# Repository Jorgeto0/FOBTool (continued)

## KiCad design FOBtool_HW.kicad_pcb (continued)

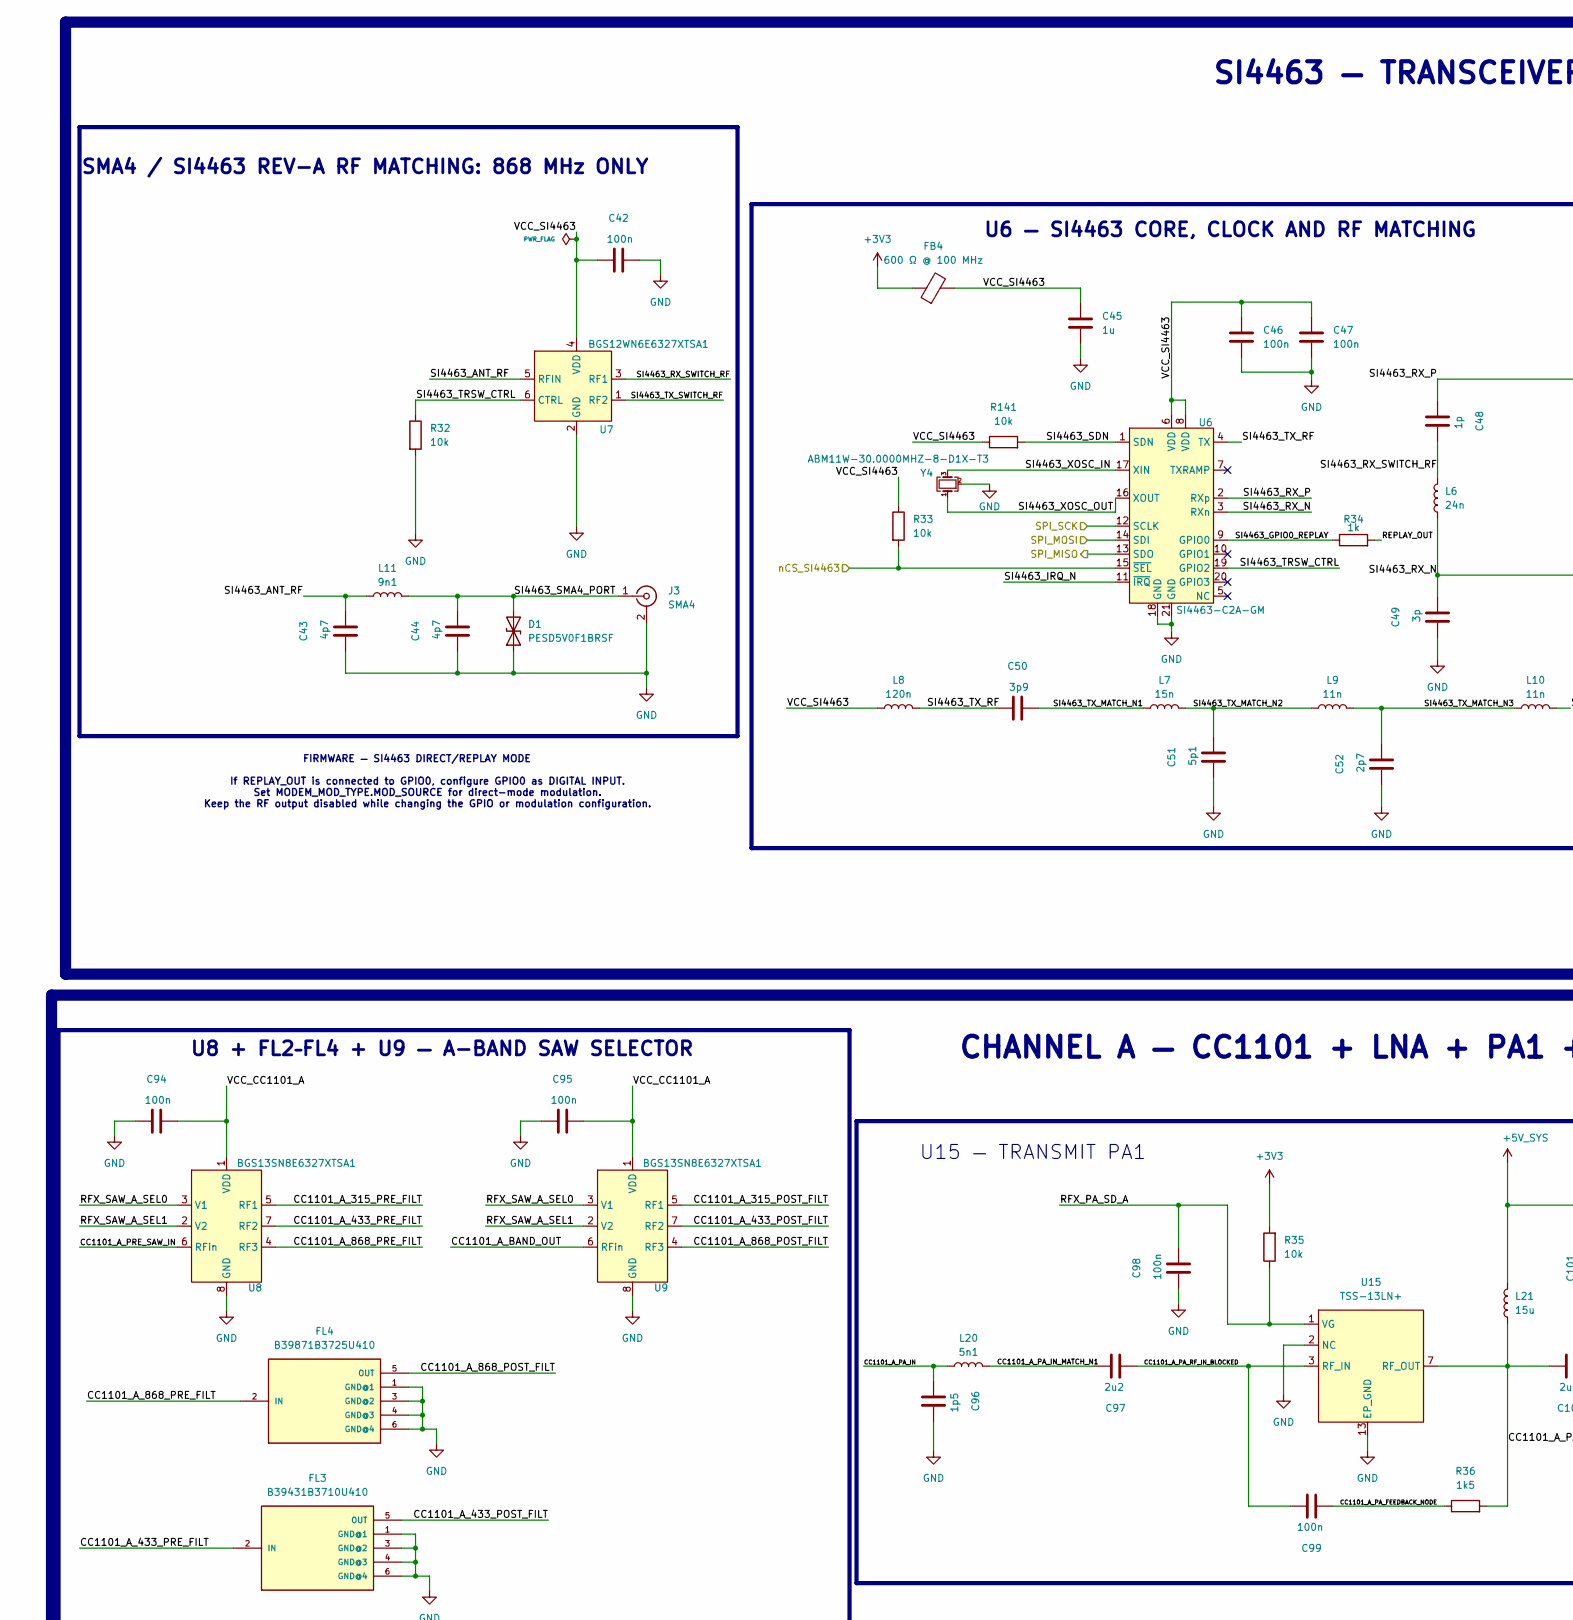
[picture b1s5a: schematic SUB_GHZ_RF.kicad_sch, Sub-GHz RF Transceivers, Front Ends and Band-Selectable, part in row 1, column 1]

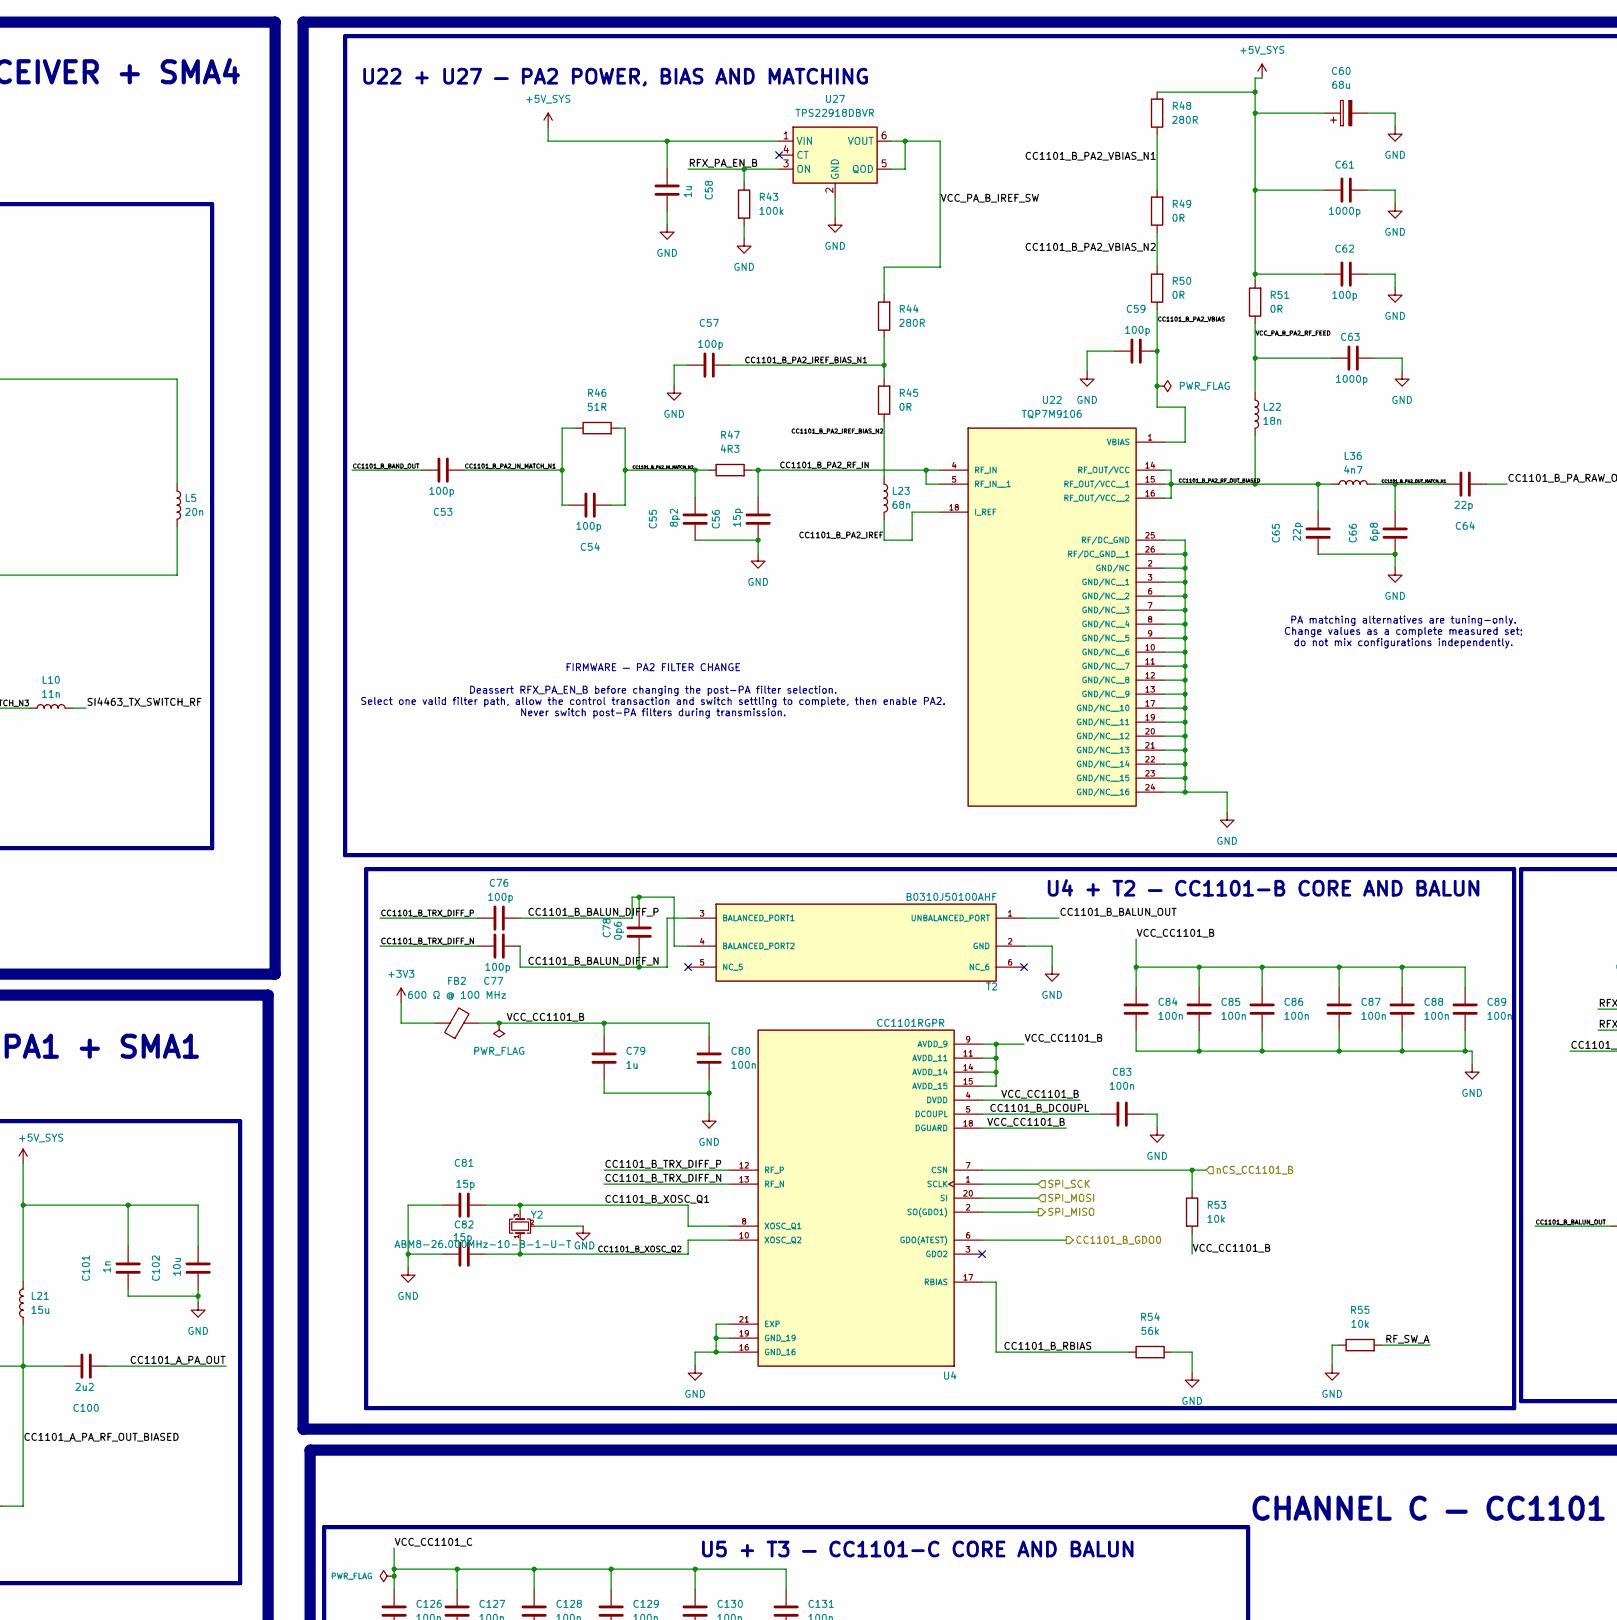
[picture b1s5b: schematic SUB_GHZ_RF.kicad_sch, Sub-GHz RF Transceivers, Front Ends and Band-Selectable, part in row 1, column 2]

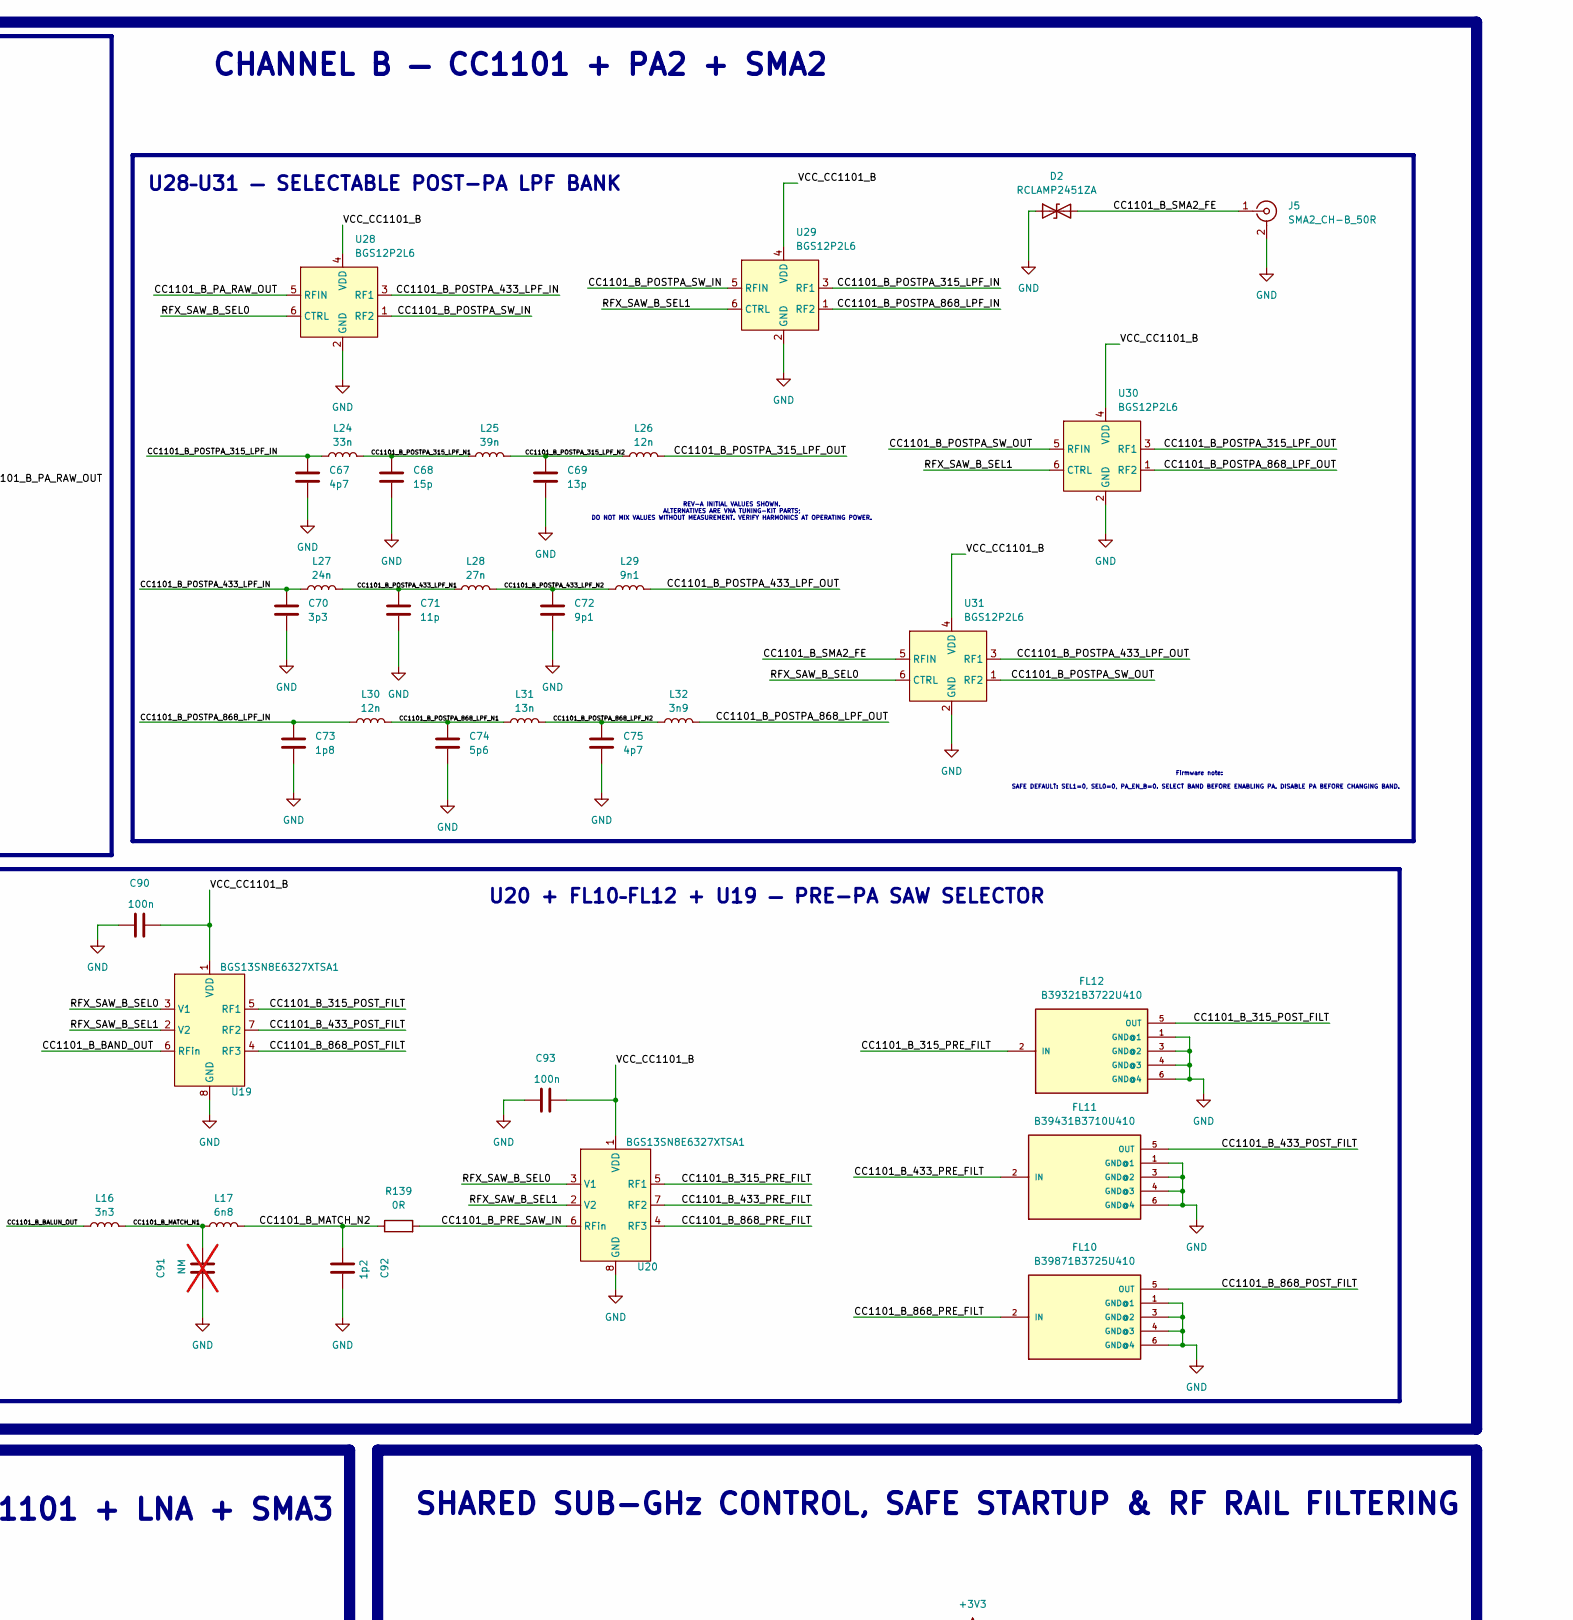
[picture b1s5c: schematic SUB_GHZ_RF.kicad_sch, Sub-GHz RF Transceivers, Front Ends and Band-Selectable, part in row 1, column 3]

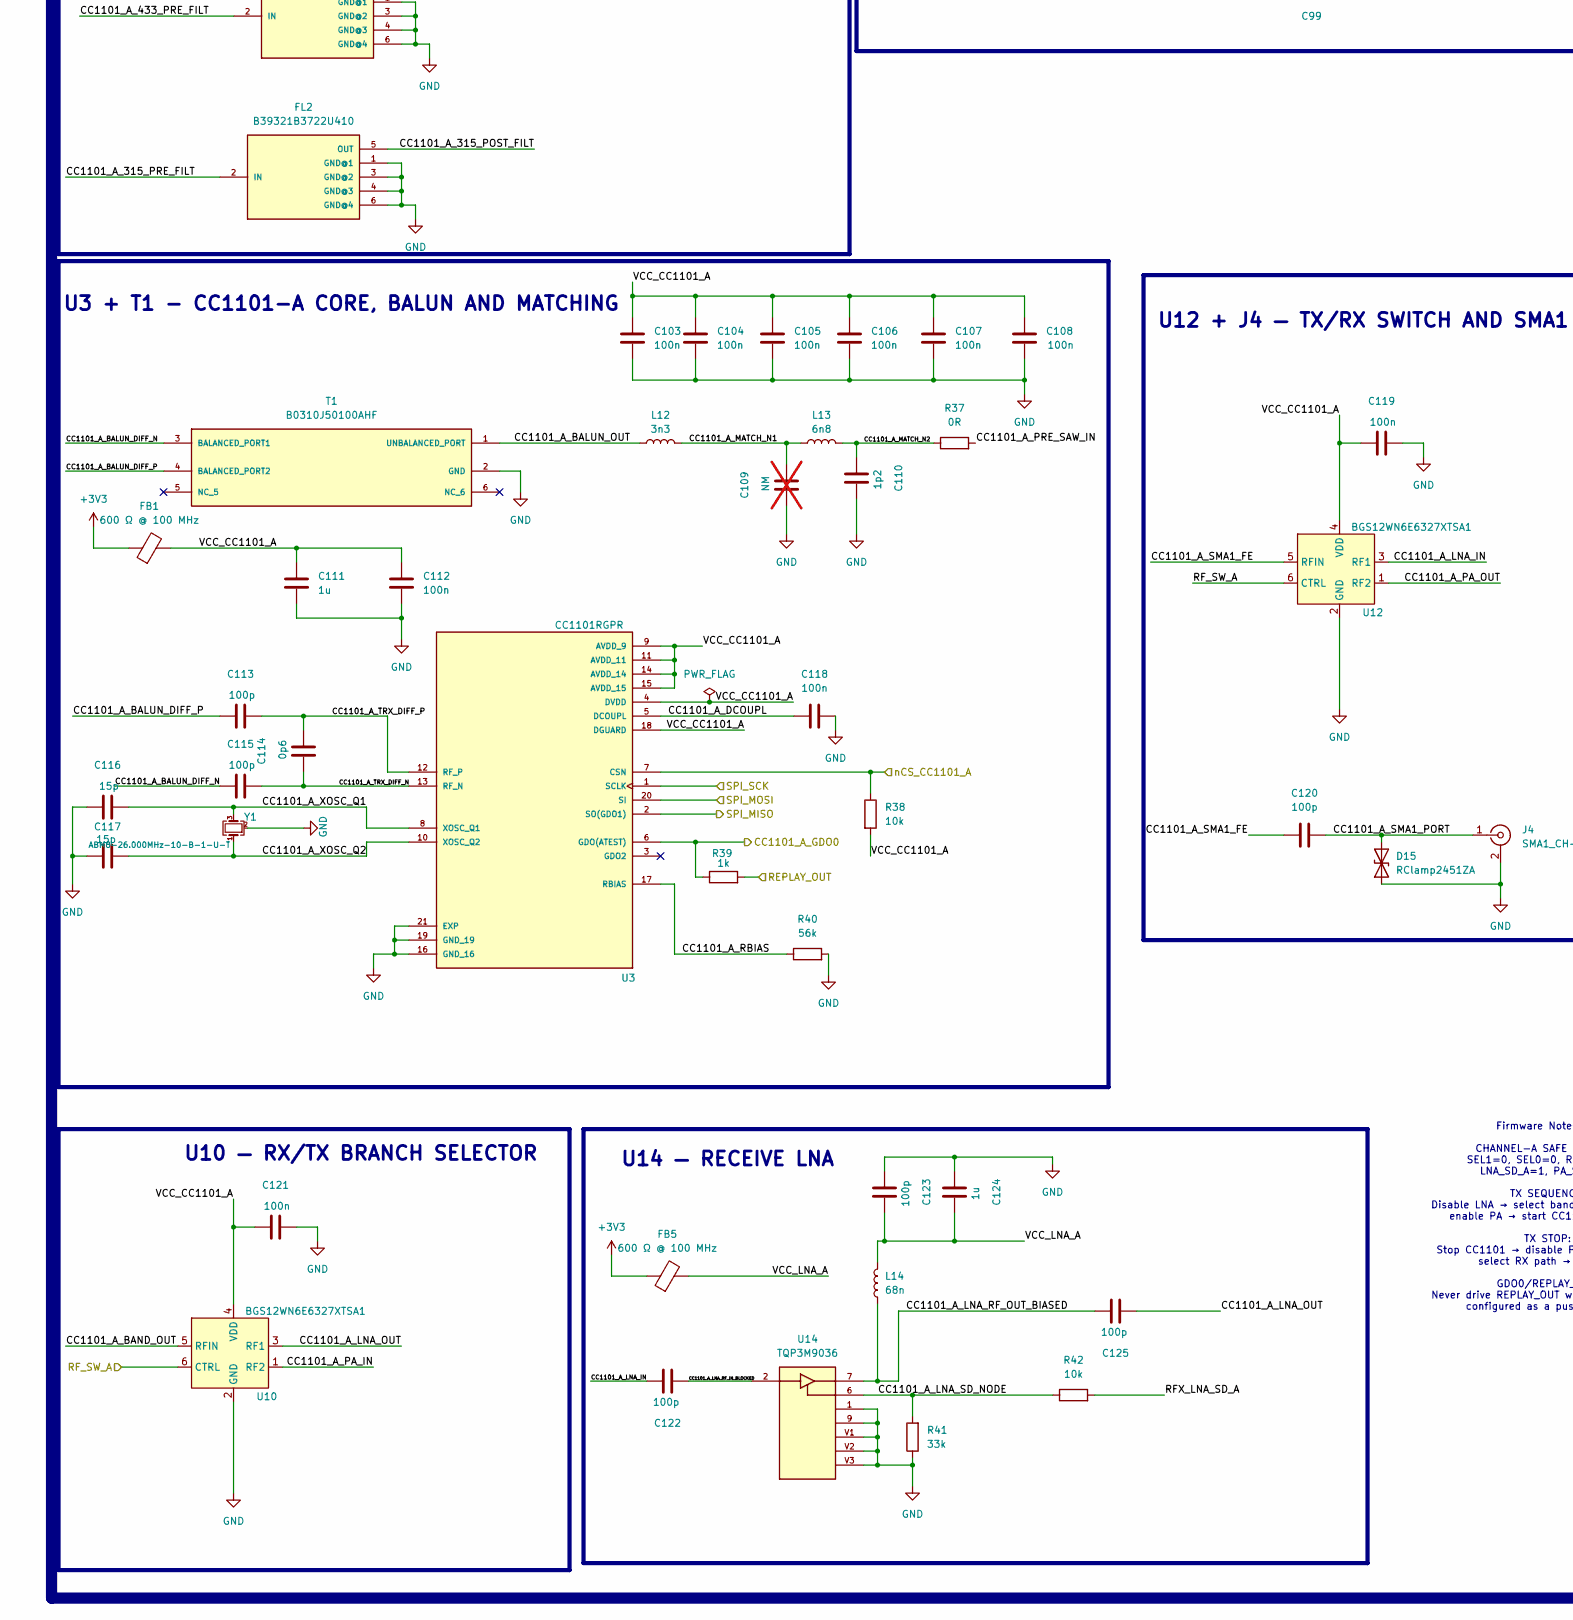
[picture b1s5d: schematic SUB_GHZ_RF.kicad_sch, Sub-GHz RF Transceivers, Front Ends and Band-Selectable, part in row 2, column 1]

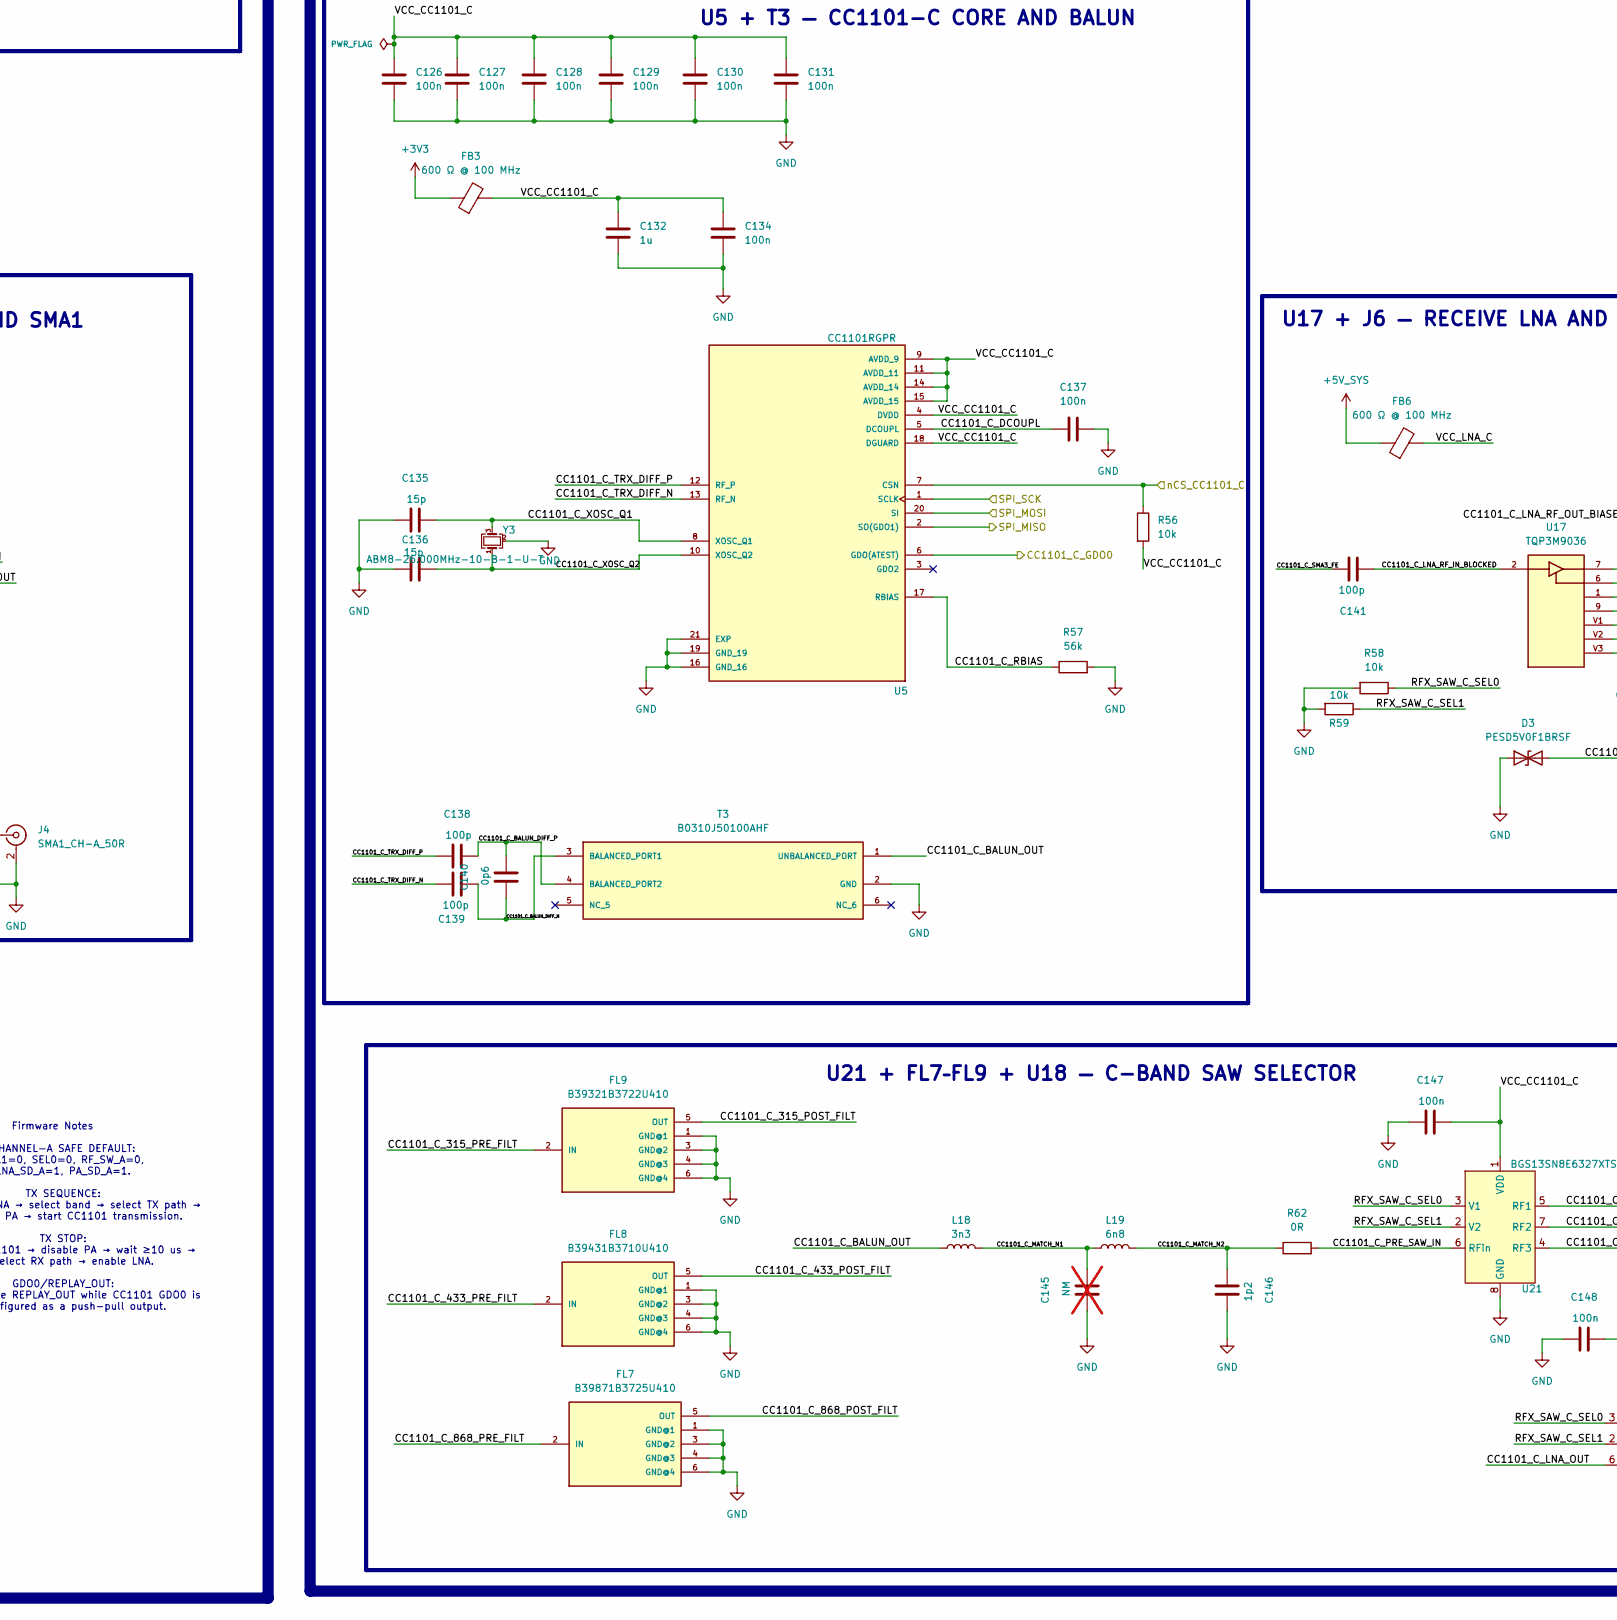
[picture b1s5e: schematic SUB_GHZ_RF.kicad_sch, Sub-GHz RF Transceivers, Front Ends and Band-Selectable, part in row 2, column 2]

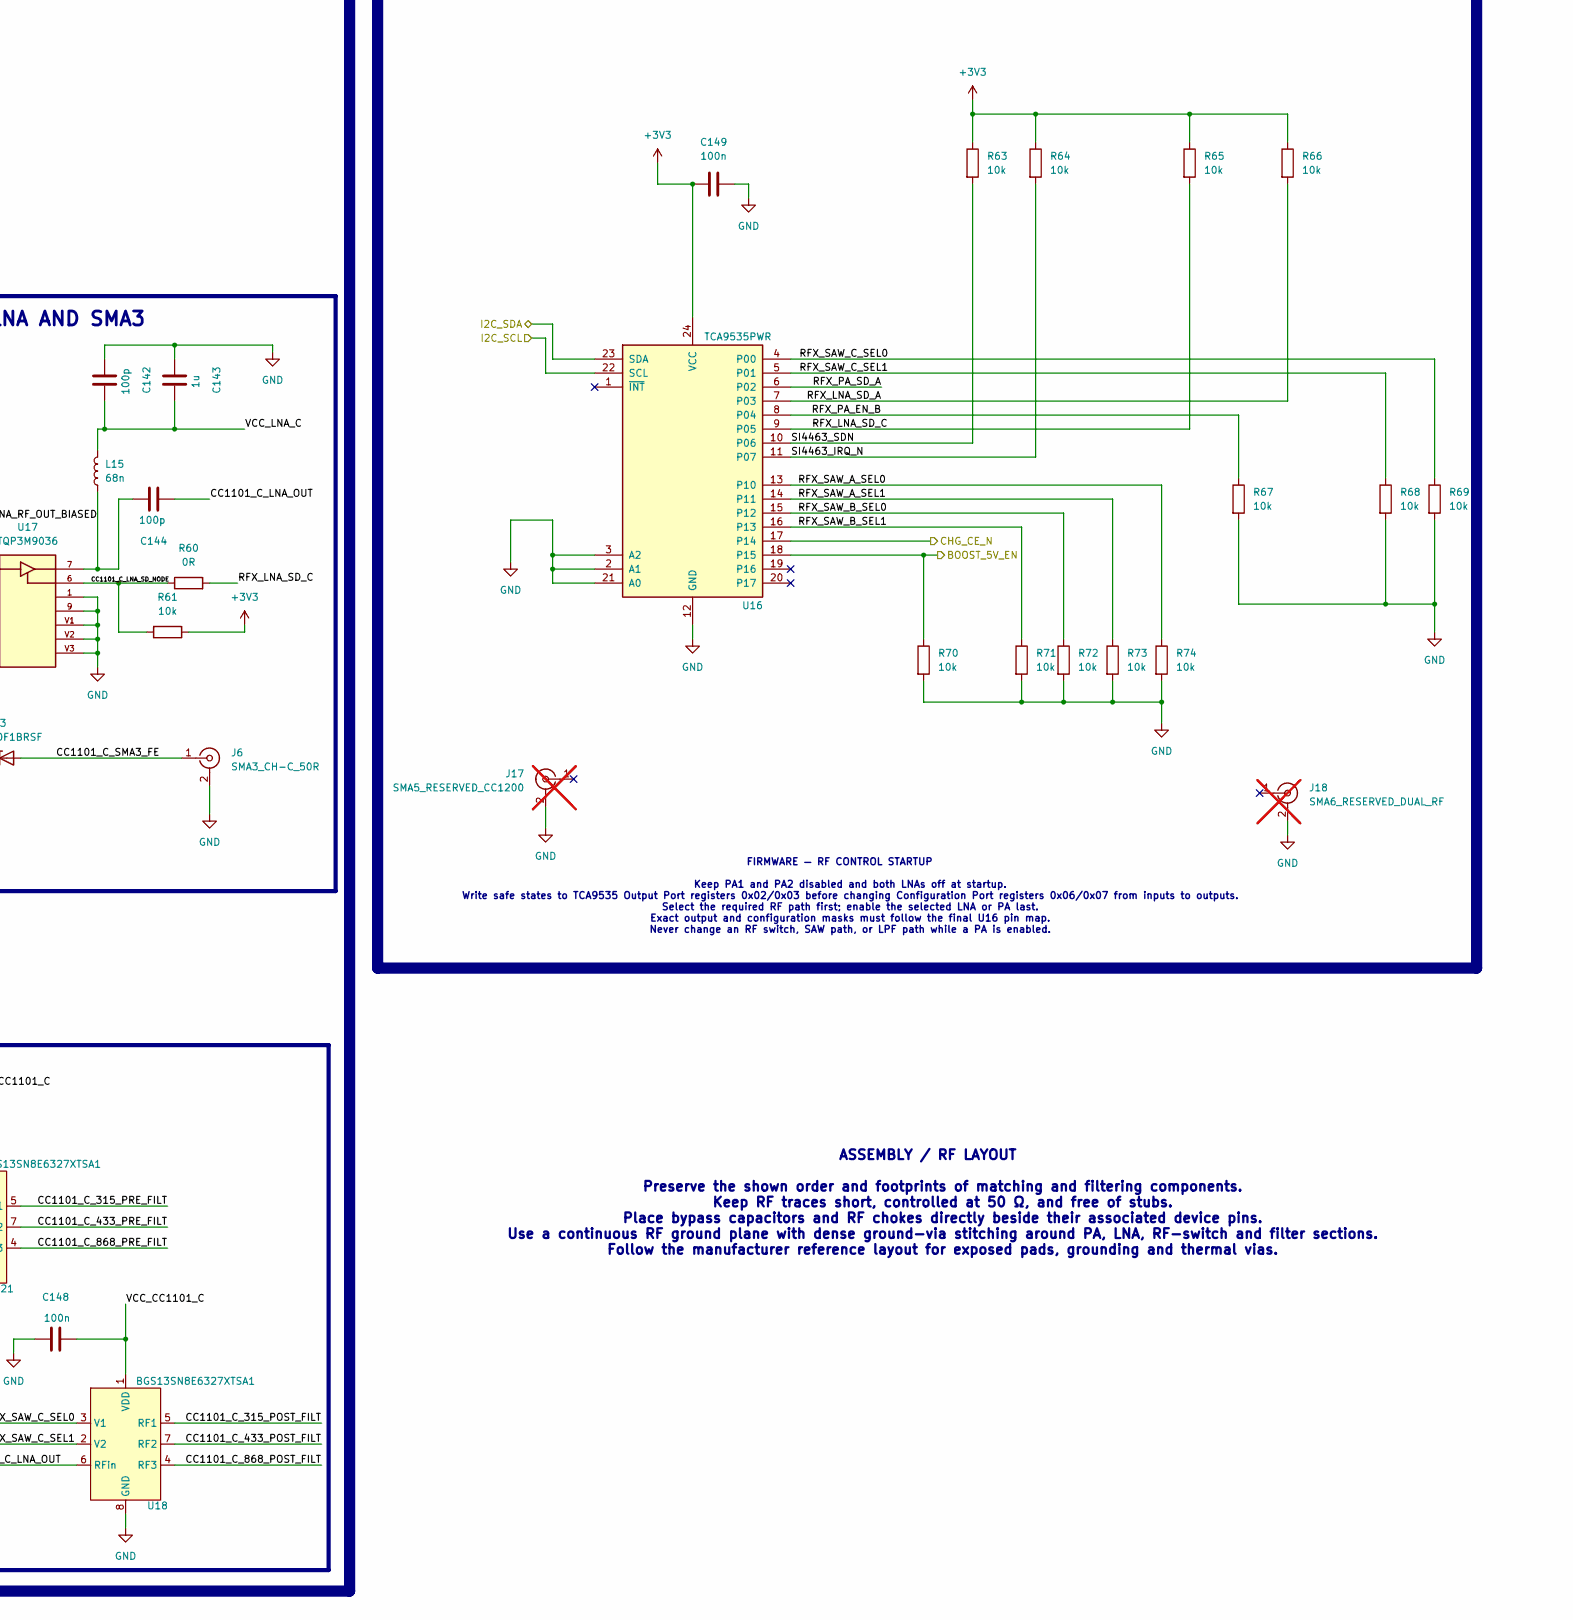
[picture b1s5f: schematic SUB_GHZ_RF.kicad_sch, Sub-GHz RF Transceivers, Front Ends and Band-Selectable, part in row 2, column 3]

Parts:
C42, C46, C47, C80, C83, C84, C85, C86, C87, C88, C89, C90, C93, C94, C95, C98, C99, C103, C104, C105, C106, C107, C108, C112, C118, C119, C121, C126, C127, C128, C129, C130, C131, C134, C137, C147, C148, C149: 100n; C_0402_1005Metric; MPN GRM155R71C104KA88D
C43, C44, C67, C75: 4p7; C_0402_1005Metric; MPN GJM1555C1H4R7BB01D
C45, C58, C79, C111, C124, C132, C143: 1u; C_0603_1608Metric; MPN GRM188R71C105KA12D
C48: 1p; C_0402_1005Metric; MPN GJM1555C1H1R0BB01D
C49: 3p; C_0402_1005Metric; MPN GJM1555C1H3R0BB01D
C50: 3p9; C_0402_1005Metric; MPN GJM1555C1H3R9BB01D
C51: 5p1; C_0402_1005Metric; MPN GJM1555C1H5R1BB01D
C52: 2p7; C_0402_1005Metric; MPN GJM1555C1H2R7BB01D
C53, C54, C57, C59, C62, C76, C77, C113, C115, C120, C122, C123, C125, C138, C139, C141, C142, C144: 100p; C_0402_1005Metric; MPN GRM1555C1H101JA01D
C55: 8p2; C_0402_1005Metric; MPN GJM1555C1H8R2DB01D
C56, C68, C81, C82, C116, C117, C135, C136: 15p; C_0402_1005Metric; MPN GJM1555C1H150JB01D
C60: 68u; CP_Panasonic_EEF-LR_7.3x4.3mm_3Terminal; MPN EEF-LR0J680R
C61, C63: 1000p; C_0402_1005Metric; MPN GRM1555C1H102JA01D
C64, C65: 22p; C_0402_1005Metric; MPN GJM1555C1H220JB01D
C66: 6p8; C_0402_1005Metric; MPN GJM1555C1H6R8CB01D
C69: 13p; C_0402_1005Metric; MPN GJM1555C1H130JB01D
C70: 3p3; C_0402_1005Metric; MPN GJM1555C1H3R3BB01D
C71: 11p; C_0402_1005Metric; MPN GJM1555C1H110JB01D
C72: 9p1; C_0402_1005Metric; MPN GJM1555C1H9R1DB01D
C73: 1p8; C_0402_1005Metric; MPN GJM1555C1H1R8BB01D
C74: 5p6; C_0402_1005Metric; MPN GJM1555C1H5R6BB01D
C78, C114, C140: 0p6; C_0402_1005Metric; MPN GJM1555C1HR60BB01D
C91, C109, C145: NM; C_0402_1005Metric; MPN N/A; not fitted
C92, C110, C146: 1p2; C_0402_1005Metric; MPN GJM1555C1H1R2BB01D
C96: 1p5; C_0402_1005Metric; MPN GJM1555C1H1R5BB01D
C97, C100: 2u2; C_0603_1608Metric; MPN GRM188R71A225KE15D
C101: 1n; C_0402_1005Metric; MPN GRM1555C1H102JA01D
C102: 10u; C_0805_2012Metric; MPN GRM21BR71A106KE51L
D1, D3: PESD5V0F1BRSF; Nexperia_DSN0603-2_0.6x0.3mm_P0.4mm; MPN PESD5V0F1BRSFYL
D2: RCLAMP2451ZA; D_Semtech_RCLAMP2451ZA_DFN0603_2; MPN RCLAMP2451ZATFT
D15: RClamp2451ZA; D_Semtech_RCLAMP2451ZA_DFN0603_2; MPN RCLAMP2451ZATFT
FB1, FB2, FB3, FB4, FB5, FB6: 600 Ω @ 100 MHz; L_0402_1005Metric; MPN BLM15AG601SN1D
FL2, FL9, FL12: B39321B3722U410; Filter_SAW_Epcos_DCC6C_3x3mm; MPN B39321B3722U410
FL3, FL8, FL11: B39431B3710U410; Filter_SAW_Epcos_DCC6C_3x3mm; MPN B39431B3710U410
FL4, FL7, FL10: B39871B3725U410; Filter_SAW_Epcos_DCC6C_3x3mm; MPN B39871B3725U410
J3: SMA4; SMA_Amphenol_132289_EdgeMount; MPN 132289
J4: SMA1_CH-A_50R; SMA_Amphenol_132289_EdgeMount; MPN 132289
J5: SMA2_CH-B_50R; SMA_Amphenol_132289_EdgeMount; MPN 132289
J6: SMA3_CH-C_50R; SMA_Amphenol_132289_EdgeMount; MPN 132289
J17: SMA5_RESERVED_CC1200; SMA_Amphenol_132289_EdgeMount; MPN 132289; not fitted
J18: SMA6_RESERVED_DUAL_RF; SMA_Amphenol_132289_EdgeMount; MPN 132289; not fitted
L5: 20n; L_0402_1005Metric; MPN LQG15WZ20NH02D
L6: 24n; L_0402_1005Metric; MPN LQG15WZ24NH02D
L7: 15n; L_0402_1005Metric; MPN LQG15HS15NJ02D
L8: 120n; L_0402_1005Metric; MPN LQG15HSR12J02D
L9, L10: 11n; L_0402_1005Metric; MPN LQG15WZ11NH02D
L11: 9n1; L_0402_1005Metric; MPN LQG15HH9N1J02D
L12, L16, L18: 3n3; L_0402_1005Metric; MPN LQG15HS3N3S02D
L13, L17, L19: 6n8; L_0402_1005Metric; MPN LQG15HH6N8J02D
L14, L15, L23: 68n; L_0402_1005Metric; MPN LQG15HS68NJ02D
L20: 5n1; L_0402_1005Metric; MPN LQG15HS5N1S02D
L21: 15u; L_Murata_LQH44PN_4.0x4.0mm; MPN LQH44PN150MPRL
L22: 18n; L_1008_2520Metric; MPN AISC-1008HQ-18NJ-T
L24: 33n; L_0603_1608Metric; MPN LQW18AN33NJ00D
L25: 39n; L_0603_1608Metric; MPN LQW18AN39NJ00D
L26, L30: 12n; L_0603_1608Metric; MPN LQW18AN12NJ00D
L27: 24n; L_0603_1608Metric; MPN LQW18AN24NJ00D
L28: 27n; L_0603_1608Metric; MPN LQW18AN27NJ00D
L29: 9n1; L_0603_1608Metric; MPN LQW18AN9N1D00D
L31: 13n; L_0603_1608Metric; MPN LQW18AN13NJ00D
L32: 3n9; L_0603_1608Metric; MPN LQW18AN3N9C00D
L36: 4n7; L_0402_1005Metric; MPN 744765047A
R32, R33, R35, R38, R42, R53, R55, R56, R58, R59, R61, R63, R64, R65, R66, R67, R68, R69, R70, R71, R72, R73, R74, R141: 10k; R_0603_1608Metric; MPN RC0603FR-0710KL
R34, R39: 1k; R_0603_1608Metric; MPN RC0603FR-071KL
R36: 1k5; R_0603_1608Metric; MPN RC0603FR-071K5L
R37, R45, R49, R50, R60, R62, R139: 0R; R_0603_1608Metric; MPN RC0603JR-070RL
R40, R54, R57: 56k; R_0603_1608Metric; MPN RC0603FR-0756KL
R41: 33k; R_0603_1608Metric; MPN RC0603FR-0733KL
R43: 100k; R_0603_1608Metric; MPN RC0603FR-07100KL
R44, R48: 280R; R_0603_1608Metric; MPN RC0603FR-07280RL
R46: 51R; R_0402_1005Metric; MPN RC0402FR-0751RL
R47: 4R3; R_0402_1005Metric; MPN RC0402FR-074R3L
R51: 0R; R_0805_2012Metric; MPN ERJ-6GEY0R00V
T1, T2, T3: B0310J50100AHF; XFMR_B0310J50100AHF; PARTREV A
U3, U4, U5: CC1101RGPR; QFN50P400X400X100-21N; PARTREV 6-May-2020
U6: SI4463-C2A-GM; QFN-20-1EP_4x4mm_P0.5mm_EP2.6x2.6mm_ThermalVias; MPN SI4463-C2A-GMR
U7, U10, U12: BGS12WN6E6327XTSA1; Infineon_PG-TSNP-6-10_0.7x1.1mm_0.7x1.1mm_P0.4mm; MPN BGS12WN6E6327XTSA1
U8, U9, U18, U19, U20, U21: BGS13SN8E6327XTSA1; Infineon_PG-TSNP-8-1_1.1x1.1mm_P0.4mm; MPN BGS13SN8E6327XTSA1
U14, U17: TQP3M9036; SON50P200X200X95-9N; PARTREV N/A
U15: TSS-13LN+; QFN-12-1EP_3x3mm_P0.51mm_EP1.45x1.45mm; MPN TSS-13LN+
U16: TCA9535PWR; TSSOP-24_4.4x7.8mm_P0.65mm; MPN TCA9535PWR
U22: TQP7M9106; QFN50P400X400X90-25N; PARTREV Rev.D
U27: TPS22918DBVR; SOT-23-6; MPN TPS22918DBVR
U28, U29, U30, U31: BGS12P2L6; Infineon_PG-TSNP-6-10_0.7x1.1mm_0.7x1.1mm_P0.4mm; MPN BGS12P2L6E6327XTSA1
Y1, Y2, Y3: ABM8-26.000MHz-10-B-1-U-T; Crystal_SMD_3225-4Pin_3.2x2.5mm; MPN ABM8-26.000MHz-10-B-1-U-T
Y4: ABM11W-30.0000MHZ-8-D1X-T3; Crystal_SMD_2016-4Pin_2.0x1.6mm; MPN ABM11W-30.0000MHZ-8-D1X-T3

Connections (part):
+3V3: C149.2, FB1.1, FB2.1, FB3.1, FB4.1, FB5.1, R35.2, R61.1, R63.1, R64.1, R65.1, R66.1, U16.24 (VCC); also elsewhere on the board
+5V_SYS: C58.1, C60.1, C61.2, C62.2, C101.2, C102.2, FB6.1, L21.2, R48.2, R51.2, U27.1 (VIN); also elsewhere on the board
/BOOST_5V_EN: R70.1, U16.18 (P15); also elsewhere on the board
/CC1101_A_GDO0: R39.1, U3.6 (GDO(ATEST)); also elsewhere on the board
/CC1101_B_GDO0: U4.6 (GDO(ATEST)); also elsewhere on the board
/CC1101_C_GDO0: U5.6 (GDO(ATEST)); also elsewhere on the board
/CHG_CE_N: U16.17 (P14); also elsewhere on the board
/I2C_SCL: U16.22 (SCL); also elsewhere on the board
/I2C_SDA: U16.23 (SDA); also elsewhere on the board
/REPLAY_OUT: R34.2, R39.2; also elsewhere on the board
/RF_SW_A: R55.2, U10.6 (CTRL), U12.6 (CTRL); also elsewhere on the board
/SPI_MISO: U3.2 (SO(GDO1)), U4.2 (SO(GDO1)), U5.2 (SO(GDO1)), U6.13 (SDO); also elsewhere on the board
/SPI_MOSI: U3.20 (SI), U4.20 (SI), U5.20 (SI), U6.14 (SDI); also elsewhere on the board
/SPI_SCK: U3.1 (SCLK), U4.1 (SCLK), U5.1 (SCLK), U6.12 (SCLK); also elsewhere on the board
/SUB_GHZ_RF/CC1101_A_315_POST_FILT: FL2.5 (OUT), U9.5 (RF1)
/SUB_GHZ_RF/CC1101_A_315_PRE_FILT: FL2.2 (IN), U8.5 (RF1)
/SUB_GHZ_RF/CC1101_A_433_POST_FILT: FL3.5 (OUT), U9.7 (RF2)
/SUB_GHZ_RF/CC1101_A_433_PRE_FILT: FL3.2 (IN), U8.7 (RF2)
/SUB_GHZ_RF/CC1101_A_868_POST_FILT: FL4.5 (OUT), U9.4 (RF3)
/SUB_GHZ_RF/CC1101_A_868_PRE_FILT: FL4.2 (IN), U8.4 (RF3)
/SUB_GHZ_RF/CC1101_A_BALUN_DIFF_N: C115.1, T1.3 (BALANCED_PORT1)
/SUB_GHZ_RF/CC1101_A_BALUN_DIFF_P: C113.1, T1.4 (BALANCED_PORT2)
/SUB_GHZ_RF/CC1101_A_BALUN_OUT: L12.1, T1.1 (UNBALANCED_PORT)
/SUB_GHZ_RF/CC1101_A_BAND_OUT: U9.6 (RFin), U10.5 (RFIN)
/SUB_GHZ_RF/CC1101_A_DCOUPL: C118.2, U3.5 (DCOUPL)
/SUB_GHZ_RF/CC1101_A_LNA_IN: C122.2, U12.3 (RF1)
/SUB_GHZ_RF/CC1101_A_LNA_OUT: C125.1, U10.3 (RF1)
/SUB_GHZ_RF/CC1101_A_LNA_RF_IN_BLOCKED: C122.1, U14.2
/SUB_GHZ_RF/CC1101_A_LNA_RF_OUT_BIASED: C125.2, L14.1, U14.7
/SUB_GHZ_RF/CC1101_A_LNA_SD_NODE: R41.2, R42.1, U14.6
/SUB_GHZ_RF/CC1101_A_MATCH_N1: C109.2, L12.2, L13.1
/SUB_GHZ_RF/CC1101_A_MATCH_N2: C110.1, L13.2, R37.1
/SUB_GHZ_RF/CC1101_A_PA_FEEDBACK_NODE: C99.1, R36.1
/SUB_GHZ_RF/CC1101_A_PA_IN: C96.1, L20.1, U10.1 (RF2)
/SUB_GHZ_RF/CC1101_A_PA_IN_MATCH_N1: C97.2, L20.2
/SUB_GHZ_RF/CC1101_A_PA_OUT: C100.1, U12.1 (RF2)
/SUB_GHZ_RF/CC1101_A_PA_RF_IN_BLOCKED: C97.1, C99.2, U15.3 (RF_IN)
/SUB_GHZ_RF/CC1101_A_PA_RF_OUT_BIASED: C100.2, L21.1, R36.2, U15.7 (RF_OUT)
/SUB_GHZ_RF/CC1101_A_PRE_SAW_IN: R37.2, U8.6 (RFin)
/SUB_GHZ_RF/CC1101_A_RBIAS: R40.1, U3.17 (RBIAS)
/SUB_GHZ_RF/CC1101_A_SMA1_FE: C120.2, U12.5 (RFIN)
/SUB_GHZ_RF/CC1101_A_SMA1_PORT: C120.1, D15.2 (A2), J4.1 (In)
/SUB_GHZ_RF/CC1101_A_TRX_DIFF_N: C114.1, C115.2, U3.13 (RF_N)
/SUB_GHZ_RF/CC1101_A_TRX_DIFF_P: C113.2, C114.2, U3.12 (RF_P)
/SUB_GHZ_RF/CC1101_A_XOSC_Q1: C116.2, U3.8 (XOSC_Q1), Y1.3
/SUB_GHZ_RF/CC1101_A_XOSC_Q2: C117.2, U3.10 (XOSC_Q2), Y1.1
/SUB_GHZ_RF/CC1101_B_315_POST_FILT: FL12.5 (OUT), U19.5 (RF1)
/SUB_GHZ_RF/CC1101_B_315_PRE_FILT: FL12.2 (IN), U20.5 (RF1)
/SUB_GHZ_RF/CC1101_B_433_POST_FILT: FL11.5 (OUT), U19.7 (RF2)
/SUB_GHZ_RF/CC1101_B_433_PRE_FILT: FL11.2 (IN), U20.7 (RF2)
/SUB_GHZ_RF/CC1101_B_868_POST_FILT: FL10.5 (OUT), U19.4 (RF3)
/SUB_GHZ_RF/CC1101_B_868_PRE_FILT: FL10.2 (IN), U20.4 (RF3)
/SUB_GHZ_RF/CC1101_B_BALUN_DIFF_N: C77.2, C78.1, T2.3 (BALANCED_PORT1)
/SUB_GHZ_RF/CC1101_B_BALUN_DIFF_P: C76.2, C78.2, T2.4 (BALANCED_PORT2)
/SUB_GHZ_RF/CC1101_B_BALUN_OUT: L16.1, T2.1 (UNBALANCED_PORT)
/SUB_GHZ_RF/CC1101_B_BAND_OUT: C53.2, U19.6 (RFin)
/SUB_GHZ_RF/CC1101_B_DCOUPL: C83.2, U4.5 (DCOUPL)
/SUB_GHZ_RF/CC1101_B_MATCH_N1: C91.2, L16.2, L17.1
/SUB_GHZ_RF/CC1101_B_MATCH_N2: C92.1, L17.2, R139.1
/SUB_GHZ_RF/CC1101_B_PA2_IN_MATCH_N1: C53.1, C54.2, R46.1
/SUB_GHZ_RF/CC1101_B_PA2_IN_MATCH_N2: C54.1, C55.2, R46.2, R47.1
/SUB_GHZ_RF/CC1101_B_PA2_IREF: L23.2, U22.18 (I_REF)
/SUB_GHZ_RF/CC1101_B_PA2_IREF_BIAS_N1: C57.2, R44.1, R45.2
/SUB_GHZ_RF/CC1101_B_PA2_IREF_BIAS_N2: L23.1, R45.1
/SUB_GHZ_RF/CC1101_B_PA2_OUT_MATCH_N1: C64.2, C66.2, L36.2
/SUB_GHZ_RF/CC1101_B_PA2_RF_IN: C56.2, R47.2, U22.4 (RF_IN), U22.5 (RF_IN__1)
/SUB_GHZ_RF/CC1101_B_PA2_RF_OUT_BIASED: C65.2, L22.2, L36.1, U22.14 (RF_OUT/VCC), U22.15 (RF_OUT/VCC__1), U22.16 (RF_OUT/VCC__2)
/SUB_GHZ_RF/CC1101_B_PA2_VBIAS: C59.2, R50.1, U22.1 (VBIAS)
/SUB_GHZ_RF/CC1101_B_PA2_VBIAS_N1: R48.1, R49.2
/SUB_GHZ_RF/CC1101_B_PA2_VBIAS_N2: R49.1, R50.2
/SUB_GHZ_RF/CC1101_B_PA_RAW_OUT: C64.1, U28.5 (RFIN)
/SUB_GHZ_RF/CC1101_B_POSTPA_315_LPF_IN: C67.1, L24.1, U29.3 (RF1)
/SUB_GHZ_RF/CC1101_B_POSTPA_315_LPF_N1: C68.1, L24.2, L25.1
/SUB_GHZ_RF/CC1101_B_POSTPA_315_LPF_N2: C69.1, L25.2, L26.1
/SUB_GHZ_RF/CC1101_B_POSTPA_315_LPF_OUT: L26.2, U30.3 (RF1)
/SUB_GHZ_RF/CC1101_B_POSTPA_433_LPF_IN: C70.1, L27.1, U28.3 (RF1)
/SUB_GHZ_RF/CC1101_B_POSTPA_433_LPF_N1: C71.1, L27.2, L28.1
/SUB_GHZ_RF/CC1101_B_POSTPA_433_LPF_N2: C72.1, L28.2, L29.1
/SUB_GHZ_RF/CC1101_B_POSTPA_433_LPF_OUT: L29.2, U31.3 (RF1)
/SUB_GHZ_RF/CC1101_B_POSTPA_868_LPF_IN: C73.1, L30.1, U29.1 (RF2)
/SUB_GHZ_RF/CC1101_B_POSTPA_868_LPF_N1: C74.1, L30.2, L31.1
/SUB_GHZ_RF/CC1101_B_POSTPA_868_LPF_N2: C75.1, L31.2, L32.1
/SUB_GHZ_RF/CC1101_B_POSTPA_868_LPF_OUT: L32.2, U30.1 (RF2)
/SUB_GHZ_RF/CC1101_B_POSTPA_SW_IN: U28.1 (RF2), U29.5 (RFIN)
/SUB_GHZ_RF/CC1101_B_POSTPA_SW_OUT: U30.5 (RFIN), U31.1 (RF2)
/SUB_GHZ_RF/CC1101_B_PRE_SAW_IN: R139.2, U20.6 (RFin)
/SUB_GHZ_RF/CC1101_B_RBIAS: R54.1, U4.17 (RBIAS)
/SUB_GHZ_RF/CC1101_B_SMA2_FE: D2.2 (A2), J5.1 (In), U31.5 (RFIN)
/SUB_GHZ_RF/CC1101_B_TRX_DIFF_N: C77.1, U4.13 (RF_N)
/SUB_GHZ_RF/CC1101_B_TRX_DIFF_P: C76.1, U4.12 (RF_P)
/SUB_GHZ_RF/CC1101_B_XOSC_Q1: C81.2, U4.8 (XOSC_Q1), Y2.3
/SUB_GHZ_RF/CC1101_B_XOSC_Q2: C82.2, U4.10 (XOSC_Q2), Y2.1
/SUB_GHZ_RF/CC1101_C_315_POST_FILT: FL9.5 (OUT), U18.5 (RF1)
/SUB_GHZ_RF/CC1101_C_315_PRE_FILT: FL9.2 (IN), U21.5 (RF1)
/SUB_GHZ_RF/CC1101_C_433_POST_FILT: FL8.5 (OUT), U18.7 (RF2)
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
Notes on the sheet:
SMA4 / SI4463 REV-A RF MATCHING: 868 MHz ONLY
U15 — TRANSMIT PA1
U12 + J4 — TX/RX SWITCH AND SMA1
U17 + J6 — RECEIVE LNA AND SMA3
CHANNEL A — CC1101 + LNA + PA1 + SMA1
U28–U31 — SELECTABLE POST-PA LPF BANK
U4 + T2 — CC1101-B CORE AND BALUN
U14 — RECEIVE LNA
U21 + FL7–FL9 + U18 — C-BAND SAW SELECTOR
Firmware note: SAFE DEFAULT: SEL1=0, SEL0=0, PA_EN_B=0. SELECT BAND BEFORE ENABLING PA. DISABLE PA BEFORE CHANGING BAND.
U5 + T3 — CC1101-C CORE AND BALUN
ASSEMBLY / RF LAYOUT Preserve the shown order and footprints of matching and filtering components. Keep RF traces short, controlled at 50 Ω, and free of stubs. Place bypass capacitors and RF chokes directly beside their associated device pins. Use a continuous RF ground plane with dense ground-via 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
SHARED SUB-GHz CONTROL, SAFE STARTUP & RF RAIL FILTERING
SI4463 — TRANSCEIVER + SMA4
REV-A INITIAL VALUES SHOWN. ALTERNATIVES ARE VNA TUNING-KIT PARTS; DO NOT MIX VALUES WITHOUT MEASUREMENT. VERIFY HARMONICS AT OPERATING POWER.
Firmware Notes CHANNEL-A SAFE DEFAULT: SEL1=0, SEL0=0, RF_SW_A=0, LNA_SD_A=1, PA_SD_A=1. TX SEQUENCE: Disable LNA → select band → select TX path → enable PA → start CC1101 transmission. TX STOP: Stop CC1101 → disable PA → wait ≥10 us → select RX path → enable LNA. GDO0/REPLAY_OUT: Never drive REPLA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
U10 — RX/TX BRANCH SELECTOR
U20 + FL10–FL12 + U19 — PRE-PA SAW SELECTOR
FIRMWARE — SI4463 DIRECT/REPLAY MODE If REPLAY_OUT is connected to GPIO0, configure GPIO0 as DIGITAL INPUT. Set MODEM_MOD_TYPE.MOD_SOURCE for direct-mode modulation. Keep the RF output disabled while changing the GPIO or modulation configuration.
FIRMWARE — PA2 FILTER CHANGE Deassert RFX_PA_EN_B before changing the post-PA filter selection. Select one valid filter path, allow the control transaction and switch settling to complete, then enable PA2. Never switch post-PA filters during transmission.
U3 + T1 - CC1101-A CORE, BALUN AND MATCHING
U8 + FL2–FL4 + U9 — A-BAND SAW SELECTOR
U6 — SI4463 CORE, CLOCK AND RF MATCHING
CHANNEL C — CC1101 + LNA + SMA3
FIRMWARE — RF CONTROL STARTUP Keep PA1 and PA2 disabled and both LNAs off at startup. Write safe states to TCA9535 Output Port registers 0x02/0x03 before changing Configuration Port registers 0x06/0x07 from inputs to outputs. Select the required RF path first; enable the selected LNA or PA last. Ex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
U22 + U27 — PA2 POWER, BIAS AND MATCHING
PA matching alternatives are tuning-only. Change values as a complete measured set; do not mix configurations independently.
CHANNEL B — CC1101 + PA2 + SMA2
